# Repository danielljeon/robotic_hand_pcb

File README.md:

# robotic_hand_pcb

Robotic hand project for actuators/power electronics and sensors/instrumentation
university courses (PCB hardware).

STM32F446RE firmware
repo: [robotic_hand](https://github.com/danielljeon/robotic_hand).

- System architecture is explained in further detail in this software repo.

---

<details markdown="1">
  <summary>Table of Contents</summary>

<!-- TOC -->
* [robotic_hand_pcb](#robotic_hand_pcb)
  * [1 Overview](#1-overview)
  * [2 Board Specifications](#2-board-specifications)
    * [2.1 Connectors](#21-connectors)
      * [2.1.1 BAT+/VIN Terminals](#211-batvin-terminals)
    * [2.2 Switches & Jumpers](#22-switches--jumpers)
    * [2.3 Test Pads](#23-test-pads)
  * [3 Release Notes](#3-release-notes)
    * [3.1 v0.1.0](#31-v010)
    * [3.2 v0.2.0](#32-v020)
  * [4 Development Process](#4-development-process)
    * [4.1 Simulations: OrCAD X (PSpice)](#41-simulations-orcad-x-pspice)
    * [4.2 PCB Design: KiCad](#42-pcb-design-kicad)
    * [4.3 Firmware: CLion and STM32CubeMX](#43-firmware-clion-and-stm32cubemx)
    * [4.4. Version Control: GitHub](#44-version-control-github)
  * [5 Switching Buck Regulator](#5-switching-buck-regulator)
    * [5.1 Load Current Estimation](#51-load-current-estimation)
    * [5.2 Switching Frequency Selection](#52-switching-frequency-selection)
    * [5.3 Inductor Selection](#53-inductor-selection)
    * [5.4 Output Capacitor Selection](#54-output-capacitor-selection)
    * [5.5 Input Capacitor Selection](#55-input-capacitor-selection)
    * [5.6 PSpice Simulation](#56-pspice-simulation)
      * [5.6.1 Schematic](#561-schematic)
      * [5.6.2 Output](#562-output)
      * [5.6.3 Fast Fourier Transform (FFT)](#563-fast-fourier-transform-fft)
  * [💖 Sponsors](#-sponsors)
    * [PCBWay](#pcbway)
      * [Why PCBWay?](#why-pcbway)
<!-- TOC -->

</details>

---

This project is sponsored by **PCBWay**. You can learn more about their valuable
support here: [💖 Sponsors/PCBWay](#pcbway).

---

## 1 Overview

|                        Hand Assembly Back                         |                         Hand Assembly Front                         |
|:-----------------------------------------------------------------:|:-------------------------------------------------------------------:|
|  |  |

|                                 Top                                 |                                  Bottom                                   |
|:-------------------------------------------------------------------:|:-------------------------------------------------------------------------:|
|           |           |
|  |  |

- Pictures show v0.1.0 production run.

---

## 2 Board Specifications

### 2.1 Connectors

| Connector          |  Ref  | Description                                                                                                              |
|--------------------|:-----:|--------------------------------------------------------------------------------------------------------------------------|
| VL53L4CD Breakout  | (J)U6 | Breakout connector for TOF sensor                                                                                        |
| USB-C 5 V power    |  J1   | Power only USB-C, primary 5 V source                                                                                     |
| Tag-Connect TC2050 |  J2   | Programming/debug connector                                                                                              |
| BAT+/VIN           |  J3   | Pin 1: (GND) Ground, Pin 2: (BAT+) Power supply (> 5 V, <= 36 V), see [2.1.1 BAT+/VIN Terminals](#211-batvin-terminals). |
| 5V Breakout        |  J4   | 5 V analog input 7                                                                                                       |
| BOOT0 jumper       |  J5   | Open for run flash memory (pull-down on open)                                                                            |
| UART Breakout      |  J6   | General purpose UART breakout                                                                                            |
| WS2812B PWM LEDs   |  J7   | 5 V Addressable LED breakout                                                                                             |
| ADC 1              |  J8   | 5 V analog input 1                                                                                                       |
| ADC 2              |  J9   | 5 V analog input 2                                                                                                       |
| ADC 3              |  J10  | 5 V analog input 3                                                                                                       |
| ADC 4              |  J11  | 5 V analog input 4                                                                                                       |
| ADC 5              |  J12  | 5 V analog input 5                                                                                                       |
| ADC 6              |  J13  | 5 V analog input 6                                                                                                       |
| ADC 7              |  J14  | 5 V analog input 7                                                                                                       |
| Unipolar Motor 1   |  J15  | Robotic finger 1 motor                                                                                                   |
| Unipolar Motor 2   |  J16  | Robotic finger 2 motor                                                                                                   |
| Unipolar Motor 3   |  J17  | Robotic finger 3 motor                                                                                                   |
| Unipolar Motor 4   |  J18  | Robotic finger 4 motor                                                                                                   |
| Unipolar Motor 5   |  J19  | Robotic finger 5 motor                                                                                                   |

- All generic breakout connectors are standard 2.54 mm pitch Harwin connectors
  except for the BAT+/VIN connector.

#### 2.1.1 BAT+/VIN Terminals

The battery or supply terminals for the LMR51430 (5 V) buck regulator are custom
sizes designed for higher gauge wires.

The **recommended supply voltage is 12 V**, however the LMR51430 has a
theoretical range up to 36 volts.

- Hole: 1.5 mm diameter.
- Pad: 2.5 mm diameter.
- Pitch: 4 mm (center-to-center distance).

### 2.2 Switches & Jumpers

| Switch/Jumper         | Ref | Description                                           |
|-----------------------|:---:|-------------------------------------------------------|
| MCU NRESET switch     | SW1 | Generic 6 mm TH button, push to reset                 |
| VL53L4CD breakout INT | JP1 | Open = no breakout, closed = bridge breakout INT line |
| BNO085 clock select   | JP2 | Open = crystal, closed = external/internal            |

### 2.3 Test Pads

| Test Pad        | Ref | Description                                                       |
|-----------------|:---:|-------------------------------------------------------------------|
| LMR51430 enable | TP1 | Buck converter enable pin (tied to VIN Battery supply by default) |

---

## 3 Release Notes

### 3.1 v0.1.0

- Production oriented 4-layer board variant.
    - Designed for single production run given course project requirement.
- Order date: 2025/02/23.
- Order number: `W837000ASB9`.

### 3.2 v0.2.0

- Updated PCB for hand reworks on `v0.1.0` to get full ADS114S08 feature
  functionality.
    - Requires software changes for this functionality, thus semantic versioning
      minor value was moved to `2`.
    - Rework shown in picture below:

---

## 4 Development Process

### 4.1 Simulations: OrCAD X (PSpice)

[OrCAD X (PSpice)](https://www.cadence.com/en_US/home/tools/pcb-design-and-analysis/analog-mixed-signal-simulation/pspice.html)
by Cadence was used for circuit simulation and evaluation.

Since this project relies heavily on Texas Instruments (TI) components (ADC ICs,
Darlington transistor arrays, and buck regulators), PSpice was chosen for design
verification and virtual testing. TI provides official PSpice models, making
simulations more accurate and reliable.

Initially, [PSpice for TI](https://www.ti.com/tool/PSPICE-FOR-TI) (a free
version limited to TI parts) was used. Upgrading to OrCAD X enabled full
compatibility and broader simulation capabilities.

### 4.2 PCB Design: KiCad

[KiCad](https://www.kicad.org/) was chosen for PCB design due to its ease of use
as a free, open-source software. Additionally, prior experience and personal
preference played a key role in the decision.

### 4.3 Firmware: CLion and STM32CubeMX

[CLion](https://www.jetbrains.com/clion/)
and [STM32CubeMX](https://www.st.com/en/development-tools/stm32cubemx.html) from
STMicroelectronics were selected based on prior experience and personal
preference. STM32CubeMX is utilized for initial component selection, pin
configuration, and HAL software generation, while CLion is used for general C
firmware development. For more details,
see [robotic_hand](https://github.com/danielljeon/robotic_hand).

### 4.4. Version Control: GitHub

[GitHub](https://github.com/) was chosen for its efficiency in version control
and support for Actions automations. These automations facilitated testing,
validation, and various manufacturing-related processes for both hardware and
software development.

---

## 5 Switching Buck Regulator

The LMR51430 was chosen for its wide input voltage range of 4.5 V to 36 V, high
output current of 3 A and overall efficiency.

> Datasheet: Datasheet: LMR51430 SLUSEF4A – JUNE 2022 – REVISED NOVEMBER 2022.

> Big thanks, as always, to the amazing publicly available resources online 👑:
> 1. [Switching Regulator PCB Design - Phil's Lab #60](https://www.youtube.com/watch?v=AmfLhT5SntE)
> 2. [Switching Regulator Component Selection & Sizing - Phil's Lab #71](https://www.youtube.com/watch?v=FqT_Ofd54fo)

### 5.1 Load Current Estimation

The expected current load is as follows:

| Load              | Current | n |
|-------------------|---------|---|
| Motors + drivers  | 500 mA  | 5 |
| WS2812B LEDs      | 60 mA   | 1 |
| 3.3 V ICs via LDO | 100 mA  | 1 |

Approximate total current draw: 2660 mA = 2.66 A at 5 V.

In a real-world engineering scenario, current draw would be estimated using more
accurate models and measured across various revisions of development boards.
However, due to budget constraints and the need to support future higher-voltage
applications, a 3 A buck regulator was chosen, as it is a commonly available and
cost-effective option.

While this provides only an 11% safety margin, it was deemed acceptable for
early research and educational purposes. In the worst-case scenario, the board
can also be powered by an external 5 V power supply if needed.

### 5.2 Switching Frequency Selection

The LMR51430 is capable of 500 kHz and 1.1 MHz switching. The design opted for
the 500 kHz configuration for reduced switching noise and its application of
motor current driving. A lower switching frequency would theoretically reduce
switching losses and improve efficiency at high current draw.

### 5.3 Inductor Selection

The following calculations are based on the recommendations provided in the
LMR51430 datasheet.

The desired peak-to-peak ripple current is given by the following:

$$\Delta i_L = \frac{V_{OUT} \times \left( V_{IN \space MAX} - V_{OUT} \right)}{V_{IN \space MAX} \times L \times f_{SW}}$$

- $L$ = Inductance driving ripple.

The minimum inductor specification is given by:

$$L_{min} = \frac{V_{\text{IN MAX}} - V_{\text{OUT}}}{I_{\text{OUT}} \times K_{\text{IND}}} \times \frac{V_{\text{OUT}}}{V_{\text{IN MAX}} \times f_{\text{SW}}}$$
$$L_{min} = \frac{12 \space \text{V} - 5 \space \text{V}}{3 \space \text{A} \times 0.3} \times \frac{5 \space \text{V}}{12 \space \text{V} \times 500 \times 10^{3} \space \text{Hz}}$$
$$L_{min} = 6.84 \times 10^{-6} \space \text{H} = 6.84 \space \mathrm{\mu H}$$

- $K_{IND}$ = Coefficient representing the inductor ripple current as a fraction
  of the maximum output current, utilizing 0.3 for this project.
    - > A reasonable value of KIND must be 20% to 60% of maximum IOUT supported
      > by the converter.
      >
      > - Datasheet section: _9.2.2.4 Inductor Selection_.
- $f_{\text{SW}}$ = Switching frequency, 500 kHz chosen.
- $V_{\text{IN MAX}}$ = Input voltage, expected 12 V with ±1 V, 13 V.
- $V_{\text{OUT}}$ = Output voltage, 5 V.
- $I_{\text{OUT}}$ = Output current, approximately 3 A.

> During an instantaneous over-current operation event, the RMS and peak
> inductor current can be high. The inductor saturation current must be higher
> than peak current limit level.
>
> In general, choose lower inductance in switching power supplies because it
> usually corresponds to faster transient response, smaller DCR, and reduced
> size for more compact designs. Too low of an inductance can generate too large
> of an inductor current ripple such that over-current protection at the full
> load can be falsely triggered and generates more inductor core loss because
> the current ripple is larger. Larger inductor current ripple also implies
> larger output voltage ripple with the same output capacitors. With peak
> current mode control,ensure there is an adequate amount of inductor ripple
> current. A larger inductor ripple current improves the comparator
> signal-to-noise ratio.
>
> - Datasheet section: _9.2.2.4 Inductor Selection_.

The final minimum inductance value of 6.84 μH closely matches the example
application values provided for a 12V input and 5V output, which uses 6.8 μH.

### 5.4 Output Capacitor Selection

> Minimize the output capacitance to keep cost and size down. The output
> capacitor or capacitors, COUT, must be chosen with care because it directly
> affects the steady state output voltage ripple, loop stability, and output
> voltage overshoot and undershoot during load current transient. The output
> voltage ripple is essentially composed of two parts. One part is caused by the
> inductor ripple current flowing through the Equivalent Series Resistance (ESR)
> of the output capacitors ... The other part is caused by the inductor current
> ripple charging and discharging the output capacitors.
>
> - Datasheet section: _9.2.2.5 Output Capacitor Selection_.

Inductor current ripple flowing through the ESR is given by:

$$\Delta V_{\text{OUT ESR}} = \Delta i_L \times \text{ESR} = K_{\text{IND}} \times I_{\text{OUT}} \times \text{ESR}$$

Inductor current ripple charging and discharging the output capacitors is given
by:

$$\Delta V_{\text{OUT C}} = \frac{\Delta i_L}{8 \times f_{\text{SW}} \times C_{\text{OUT}}} = \frac{K_{\text{IND}} \times I_{\text{OUT}}}{8 \times f_{\text{SW}} \times C_{\text{OUT}}}$$

- $K_{\text{IND}}$ = target ripple ratio of the inductor
  current ($\Delta i L / I_{\text{OUT}}$).

The minimum output capacitance needed for a specified output voltage overshoot
and undershoot is given by:

$$C_{\text{OUT}} > \frac{1}{2} \times \frac{8 \times (I_{\text{OH}} - I_{\text{OL}})}{f_{\text{SW}} \times \Delta V_{\text{OUT SHOOT}}}$$

- $I_{\text{OL}}$ = low level output current during load transient.
- $I_{\text{OH}}$ = high level output current during load transient.
- $V_{\text{OUT SHOOT}}$ = target output voltage overshoot or undershoot.

For this project a target output ripple is arbitrarily set for 30 mV and the
ripple ratio of inductor current is set to 0.3.

- $\Delta V_{\text{OUT ESR}} = \Delta V_{\text{OUT C}} = 30 mV$
- $K_{\text{IND}} = 0.3$

This yields ESR < 75 mΩ and output capacitance > 14 μF.

### 5.5 Input Capacitor Selection

> The LMR51430 device requires a high frequency input decoupling capacitor or
> capacitor. The typical recommended value for the high frequency decoupling
> capacitor is 4.7 μF or higher. TI recommends a high-quality ceramic type X5R
> or X7R with a sufficient voltage rating. The voltage rating must be greater
> than the maximum input voltage. To compensate the derating of ceramic
> capacitors, TI recommends a voltage rating of twice the maximum input voltage.
>
> - Datasheet section: _9.2.2.5 Output Capacitor Selection_.

### 5.6 PSpice Simulation

Due to the limited availability of publicly accessible PSpice models, the
LMR51420 model was used instead. Based on datasheet specifications, the 2A
variant of the LMR514x0 series appears largely similar, with the primary
difference being the requirement for a 10 μH inductor.

#### 5.6.1 Schematic

To simulate sudden current loads, a 3.3 Ω load (drawing 1.5 A at 5 V) is added
and set to switch at 4.2 ms. The switch has a transition time of 15 μs.

#### 5.6.2 Output

#### 5.6.3 Fast Fourier Transform (FFT)

For this simulation run, the fundamental frequency was found to be 492.400 kHz
with a resultant amplitude of 1.1316. Due to the short simulation duration, the
time required to ramp up to the final voltage, and the handling of sudden loads,
it is hypothesized that the FFT results deviate slightly from the expected 500
kHz.

---

## 💖 Sponsors

### PCBWay

This project is sponsored by [**PCBWay**](https://www.pcbway.com), whose PCB
manufacturing services are essential in producing high-quality prototypes for
its development. Their support ensures reliable boards that meet the project's
demands.

#### Why PCBWay?

PCBWay stands out for their exceptional services and commitment to the
community:

- **PCB Manufacturing**: High-quality fabrication with options for multilayer,
  rigid-flex, and advanced designs.
- **PCB Assembly**: Comprehensive solutions, including soldering, component
  sourcing, and assembly.
- **CNC Machining & 3D Printing**: Additional prototyping options to support
  complete product development.
- **Fast Turnaround**: Reliable and quick production times to keep projects on
  schedule.
- **Support for Open Source & Education**: PCBWay actively sponsors projects and
  provides educational resources like tutorials, videos, and documentation,
  empowering developers and hobbyists.
    - This commitment to education and open-source advocacy was a key factor in
      choosing them as a partner 🙂.

Their dedication to professional-grade services and fostering innovation makes
PCBWay an invaluable partner in bringing this project to life.

Learn more here: [Why PCBWay?](https://www.pcbway.com/why.html)

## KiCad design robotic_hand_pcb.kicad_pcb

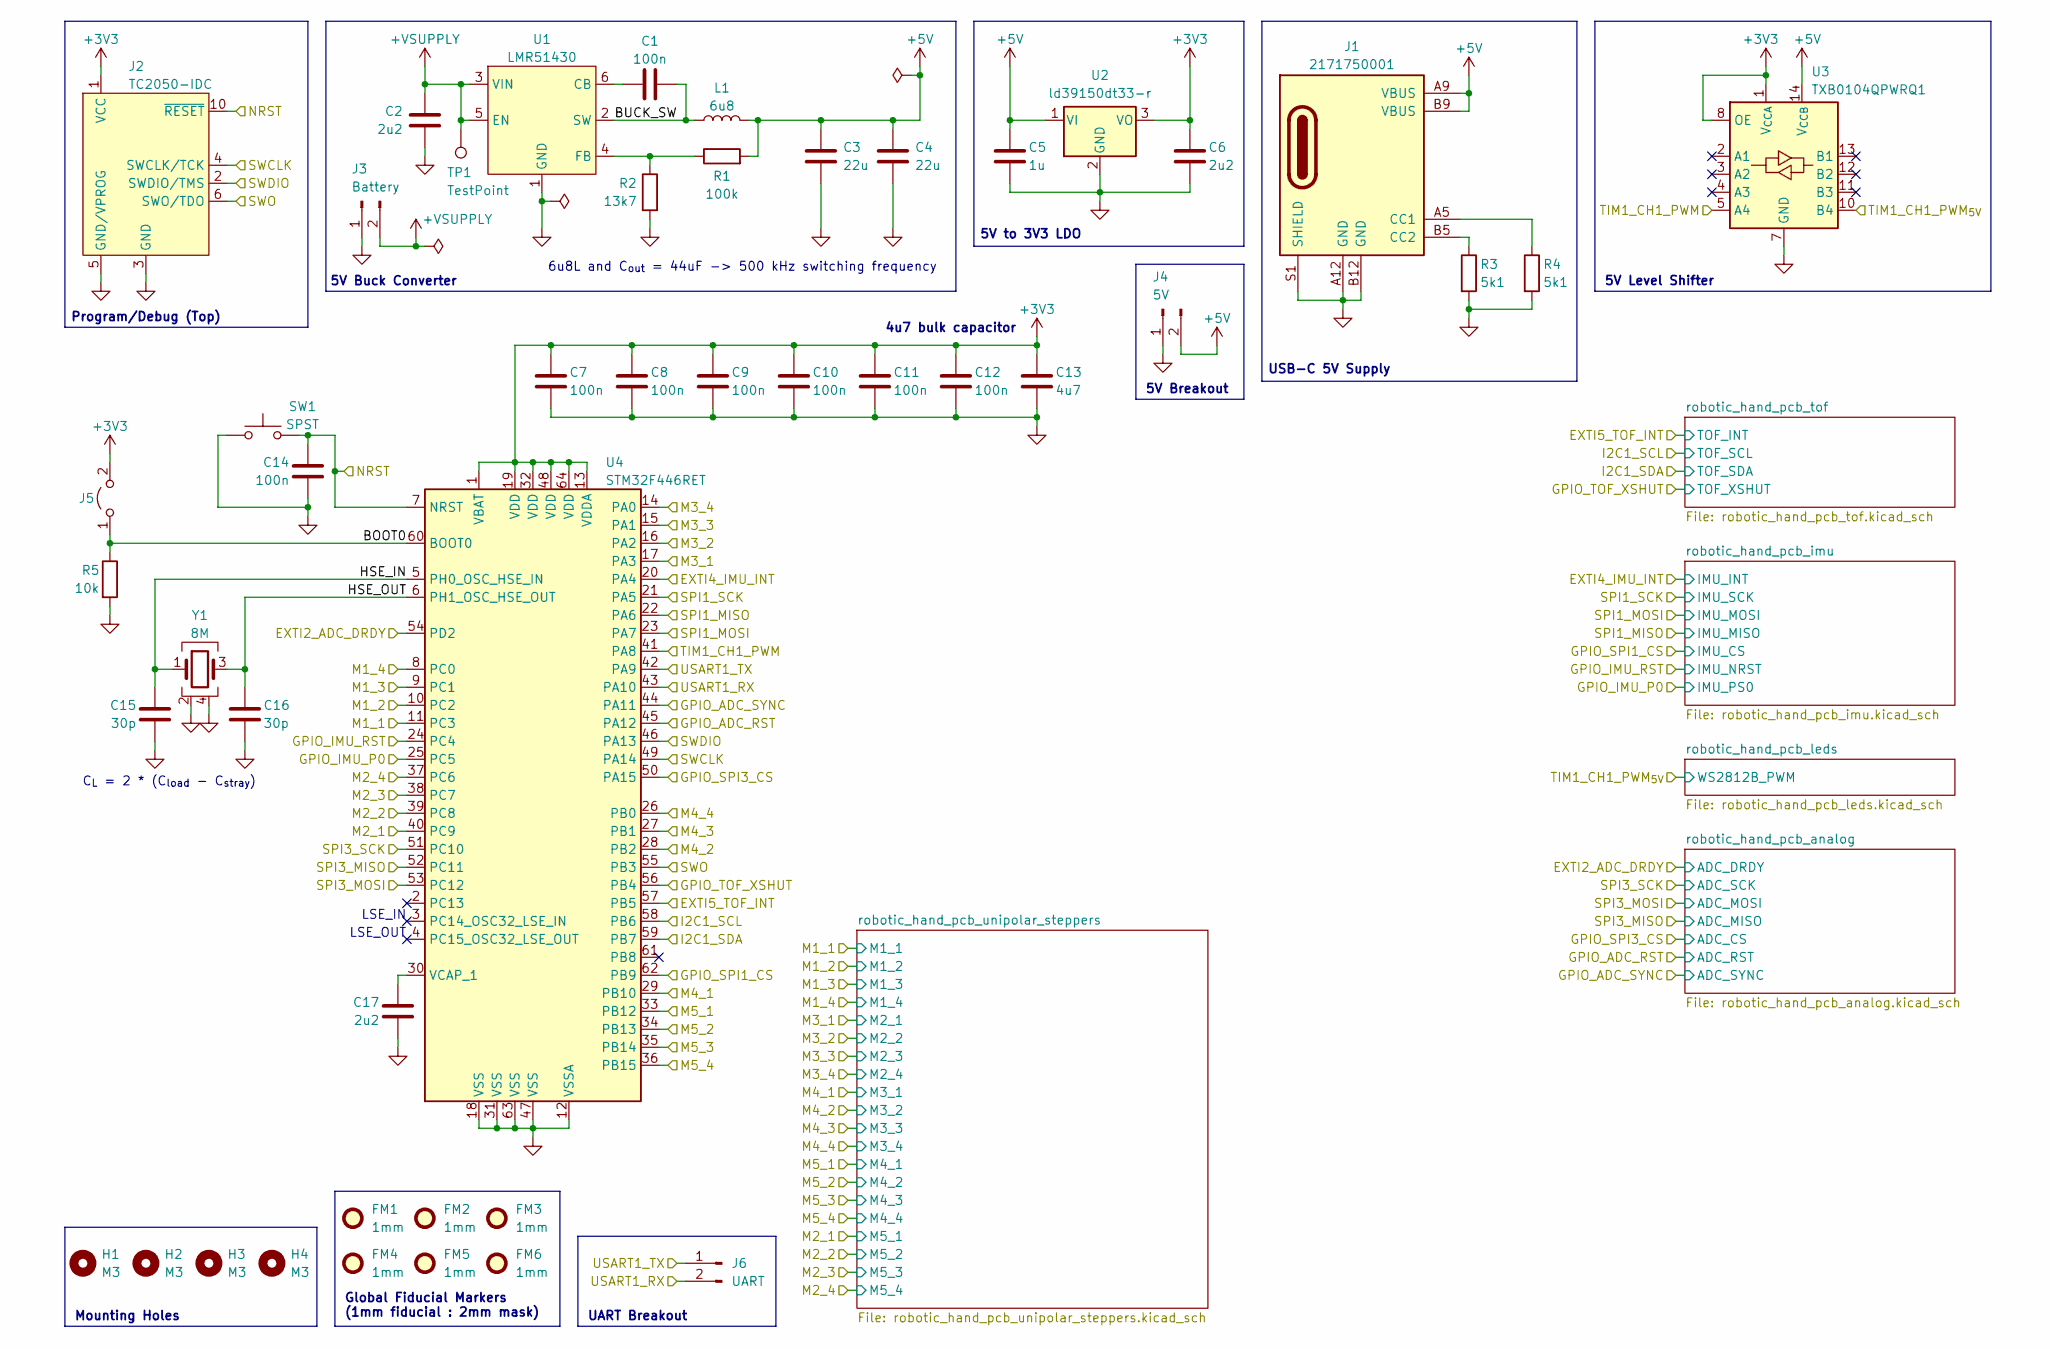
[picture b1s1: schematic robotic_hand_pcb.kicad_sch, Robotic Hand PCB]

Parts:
C1: 100n; C_0805_2012Metric
C2: 2u2; C_0805_2012Metric
C3, C4: 22u; C_1210_3225Metric
C5: 1u; C_0603_1608Metric
C6, C17: 2u2; C_0603_1608Metric
C7, C8, C9, C10, C11, C12, C14: 100n; C_0603_1608Metric
C13: 4u7; C_0603_1608Metric
C15, C16: 30p; C_0402_1005Metric
FM1, FM2, FM3, FM4, FM5, FM6: 1mm; Fiducial_1mm_Mask2mm
H1, H2, H3, H4: M3; MountingHole_3.2mm_M3
J1: 2171750001; molex_2171750001_usb_c_6p; Manufacturer Part Number 2171750001
J2: TC2050-IDC; tag_connect_tc2050-idc; Manufacturer Part Number TC2050-IDC
J3: Battery; battery
J4: 5V; PinHeader_1x02_P2.54mm_Vertical
J5: harwin_2p_2-54_jumper_open; Manufacturer Part Number M20-9990246
J6: UART; PinHeader_1x02_P2.54mm_Vertical
L1: 6u8; vishay_ihlp-2525cz
R1: 100k; R_0603_1608Metric
R2: 13k7; R_0603_1608Metric
R3, R4: 5k1; R_0603_1608Metric
R5: 10k; R_0603_1608Metric
SW1: SPST; SW_PUSH_6mm
TP1: TestPoint; TestPoint_Pad_D2.5mm
U1: LMR51430; lmr51430; Manufacturer Part Number LMR51430
U2: ld39150dt33-r; to-252-2_dpak-2-leg; Manufacturer Part Number LD39150DT33-R
U3: TXB0104QPWRQ1; txb0104qpwrq1; Manufacturer Part Number TXB0104QPWRQ1
U4: STM32F446RET; LQFP-64_10x10mm_P0.5mm; Manufacturer Part Number STM32F446RE
Y1: 8M; ecs_ecx-64; Manufacturer Part Number ECS-80-18-23B-JTN-TR

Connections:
+3V3: C6.1, C7.1, C8.1, C9.1, C10.1, C11.1, C12.1, C13.1, J2.1 (VCC), J5.2, U2.3 (VO), U3.1 (V_{CCA}), U3.8 (OE), U4.1 (VBAT), U4.13 (VDDA), U4.19 (VDD), U4.32 (VDD), U4.48 (VDD), U4.64 (VDD); also elsewhere on the board
+5V: C3.2, C4.2, C5.1, J1.A9 (VBUS), J1.B9 (VBUS), J4.2, L1.2, R1.2, U2.1 (VI), U3.14 (V_{CCB}); also elsewhere on the board
+VSUPPLY: C2.1, J3.2, TP1.1, U1.3 (VIN), U1.5 (EN)
/BOOT0: J5.1, R5.1, U4.60 (BOOT0)
/BUCK_SW: C1.2, L1.1, U1.2 (SW)
/EXTI2_ADC_DRDY: U4.54 (PD2); also elsewhere on the board
/EXTI4_IMU_INT: U4.20 (PA4); also elsewhere on the board
/EXTI5_TOF_INT: U4.57 (PB5); also elsewhere on the board
/GPIO_ADC_RST: U4.45 (PA12); also elsewhere on the board
/GPIO_ADC_SYNC: U4.44 (PA11); also elsewhere on the board
/GPIO_IMU_P0: U4.25 (PC5); also elsewhere on the board
/GPIO_IMU_RST: U4.24 (PC4); also elsewhere on the board
/GPIO_SPI1_CS: U4.62 (PB9); also elsewhere on the board
/GPIO_SPI3_CS: U4.50 (PA15); also elsewhere on the board
/GPIO_TOF_XSHUT: U4.56 (PB4); also elsewhere on the board
/HSE_IN: C15.1, U4.5 (PH0_OSC_HSE_IN), Y1.1
/HSE_OUT: C16.1, U4.6 (PH1_OSC_HSE_OUT), Y1.3
/I2C1_SCL: U4.58 (PB6); also elsewhere on the board
/I2C1_SDA: U4.59 (PB7); also elsewhere on the board
/M1_1: U4.11 (PC3); also elsewhere on the board
/M1_2: U4.10 (PC2); also elsewhere on the board
/M1_3: U4.9 (PC1); also elsewhere on the board
/M1_4: U4.8 (PC0); also elsewhere on the board
/M2_1: U4.40 (PC9); also elsewhere on the board
/M2_2: U4.39 (PC8); also elsewhere on the board
/M2_3: U4.38 (PC7); also elsewhere on the board
/M2_4: U4.37 (PC6); also elsewhere on the board
/M3_1: U4.17 (PA3); also elsewhere on the board
/M3_2: U4.16 (PA2); also elsewhere on the board
/M3_3: U4.15 (PA1); also elsewhere on the board
/M3_4: U4.14 (PA0); also elsewhere on the board
/M4_1: U4.29 (PB10); also elsewhere on the board
/M4_2: U4.28 (PB2); also elsewhere on the board
/M4_3: U4.27 (PB1); also elsewhere on the board
/M4_4: U4.26 (PB0); also elsewhere on the board
/M5_1: U4.33 (PB12); also elsewhere on the board
/M5_2: U4.34 (PB13); also elsewhere on the board
/M5_3: U4.35 (PB14); also elsewhere on the board
/M5_4: U4.36 (PB15); also elsewhere on the board
/NRST: C14.2, J2.10 (~RESET), SW1.2, U4.7 (NRST)
/SPI1_MISO: U4.22 (PA6); also elsewhere on the board
/SPI1_MOSI: U4.23 (PA7); also elsewhere on the board
/SPI1_SCK: U4.21 (PA5); also elsewhere on the board
/SPI3_MISO: U4.52 (PC11); also elsewhere on the board
/SPI3_MOSI: U4.53 (PC12); also elsewhere on the board
/SPI3_SCK: U4.51 (PC10); also elsewhere on the board
/SWCLK: J2.4 (SWCLK/TCK), U4.49 (PA14)
/SWDIO: J2.2 (SWDIO/TMS), U4.46 (PA13)
/SWO: J2.6 (SWO/TDO), U4.55 (PB3)
/TIM1_CH1_PWM: U3.5 (A4), U4.41 (PA8)
/TIM1_CH1_PWM_{5V}: U3.10 (B4); also elsewhere on the board
/USART1_RX: J6.2, U4.43 (PA10)
/USART1_TX: J6.1, U4.42 (PA9)
GND: C2.2, C3.1, C4.1, C5.2, C6.2, C7.2, C8.2, C9.2, C10.2, C11.2, C12.2, C13.2, C14.1, C15.2, C16.2, C17.2, J1.A12 (GND), J1.B12 (GND), J1.S1 (SHIELD), J2.3 (GND), J2.5 (GND/VPROG), J3.1, J4.1, R2.2, R3.2, R4.2, R5.2, SW1.1, U1.1 (GND), U2.2 (GND), U3.7 (GND), U4.12 (VSSA), U4.18 (VSS), U4.31 (VSS), U4.47 (VSS), U4.63 (VSS), Y1.2, Y1.4; also elsewhere on the board
unnamed: J1.A5 (CC1), R4.1
unnamed: J1.B5 (CC2), R3.1
unnamed: C1.1, U1.6 (CB)
unnamed: R1.1, R2.1, U1.4 (FB)
unnamed: C17.1, U4.30 (VCAP_1)

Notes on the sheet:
LSE_OUT
5V Buck Converter
5V Breakout
4u7 bulk capacitor
Program/Debug (Top)
UART Breakout
Global Fiducial Markers (1mm fiducial : 2mm mask)
C_{L} = 2 * (C_{load} - C_{stray})
USB-C 5V Supply
LSE_IN
Mounting Holes
5V Level Shifter
6u8L and C_{out} = 44uF -> 500 kHz switching frequency
5V to 3V3 LDO

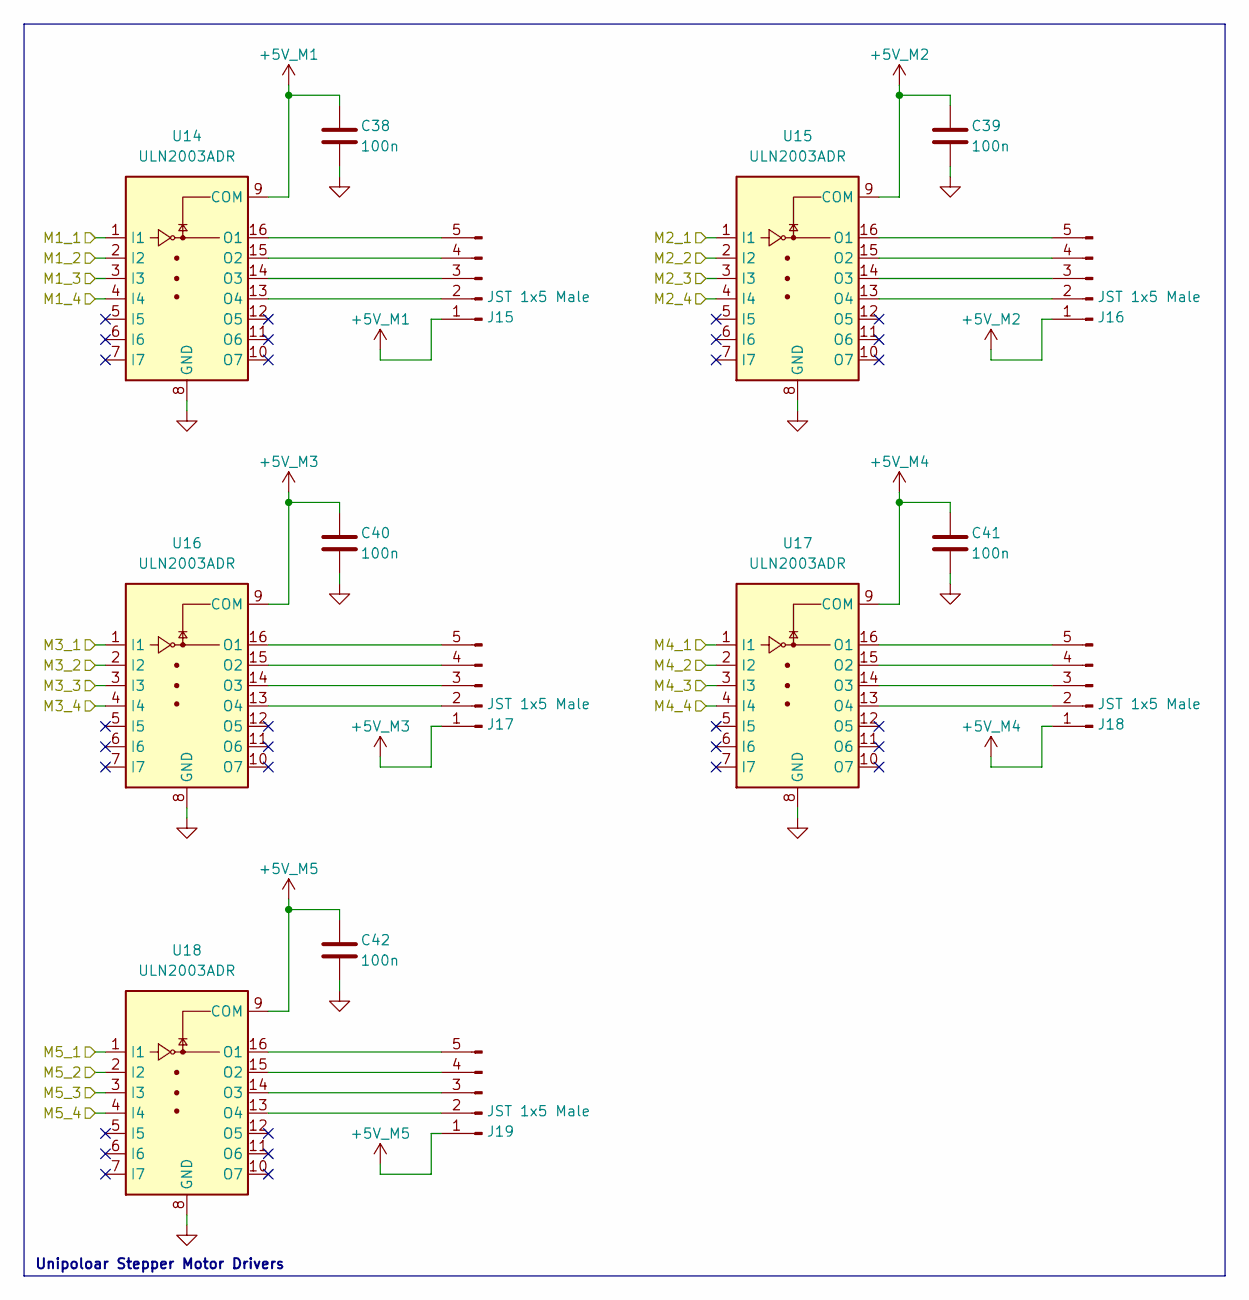
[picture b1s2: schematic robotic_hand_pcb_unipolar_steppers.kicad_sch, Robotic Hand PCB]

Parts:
C38, C39, C40, C41, C42: 100n; C_0603_1608Metric
J15, J16, J17, J18, J19: JST 1x5 Male; PinHeader_1x05_P2.54mm_Vertical
U14, U15, U16, U17, U18: ULN2003ADR; SOIC-16_3.9x9.9mm_P1.27mm

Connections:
+5V_M1: C38.1, J15.1, U14.9 (COM); also elsewhere on the board
+5V_M2: C39.1, J16.1, U15.9 (COM); also elsewhere on the board
+5V_M3: C40.1, J17.1, U16.9 (COM); also elsewhere on the board
+5V_M4: C41.1, J18.1, U17.9 (COM); also elsewhere on the board
+5V_M5: C42.1, J19.1, U18.9 (COM); also elsewhere on the board
/M1_1: U14.1 (I1); also elsewhere on the board
/M1_2: U14.2 (I2); also elsewhere on the board
/M1_3: U14.3 (I3); also elsewhere on the board
/M1_4: U14.4 (I4); also elsewhere on the board
/M2_1: U18.1 (I1); also elsewhere on the board
/M2_2: U18.2 (I2); also elsewhere on the board
/M2_3: U18.3 (I3); also elsewhere on the board
/M2_4: U18.4 (I4); also elsewhere on the board
/M3_1: U15.1 (I1); also elsewhere on the board
/M3_2: U15.2 (I2); also elsewhere on the board
/M3_3: U15.3 (I3); also elsewhere on the board
/M3_4: U15.4 (I4); also elsewhere on the board
/M4_1: U16.1 (I1); also elsewhere on the board
/M4_2: U16.2 (I2); also elsewhere on the board
/M4_3: U16.3 (I3); also elsewhere on the board
/M4_4: U16.4 (I4); also elsewhere on the board
/M5_1: U17.1 (I1); also elsewhere on the board
/M5_2: U17.2 (I2); also elsewhere on the board
/M5_3: U17.3 (I3); also elsewhere on the board
/M5_4: U17.4 (I4); also elsewhere on the board
GND: C38.2, C39.2, C40.2, C41.2, C42.2, U14.8 (GND), U15.8 (GND), U16.8 (GND), U17.8 (GND), U18.8 (GND); also elsewhere on the board
unnamed: J15.2, U14.13 (O4)
unnamed: J15.3, U14.14 (O3)
unnamed: J15.4, U14.15 (O2)
unnamed: J15.5, U14.16 (O1)
unnamed: J16.2, U15.13 (O4)
unnamed: J16.3, U15.14 (O3)
unnamed: J16.4, U15.15 (O2)
unnamed: J16.5, U15.16 (O1)
unnamed: J17.2, U16.13 (O4)
unnamed: J17.3, U16.14 (O3)
unnamed: J17.4, U16.15 (O2)
unnamed: J17.5, U16.16 (O1)
unnamed: J18.2, U17.13 (O4)
unnamed: J18.3, U17.14 (O3)
unnamed: J18.4, U17.15 (O2)
unnamed: J18.5, U17.16 (O1)
unnamed: J19.2, U18.13 (O4)
unnamed: J19.3, U18.14 (O3)
unnamed: J19.4, U18.15 (O2)
unnamed: J19.5, U18.16 (O1)

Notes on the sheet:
Unipoloar Stepper Motor Drivers

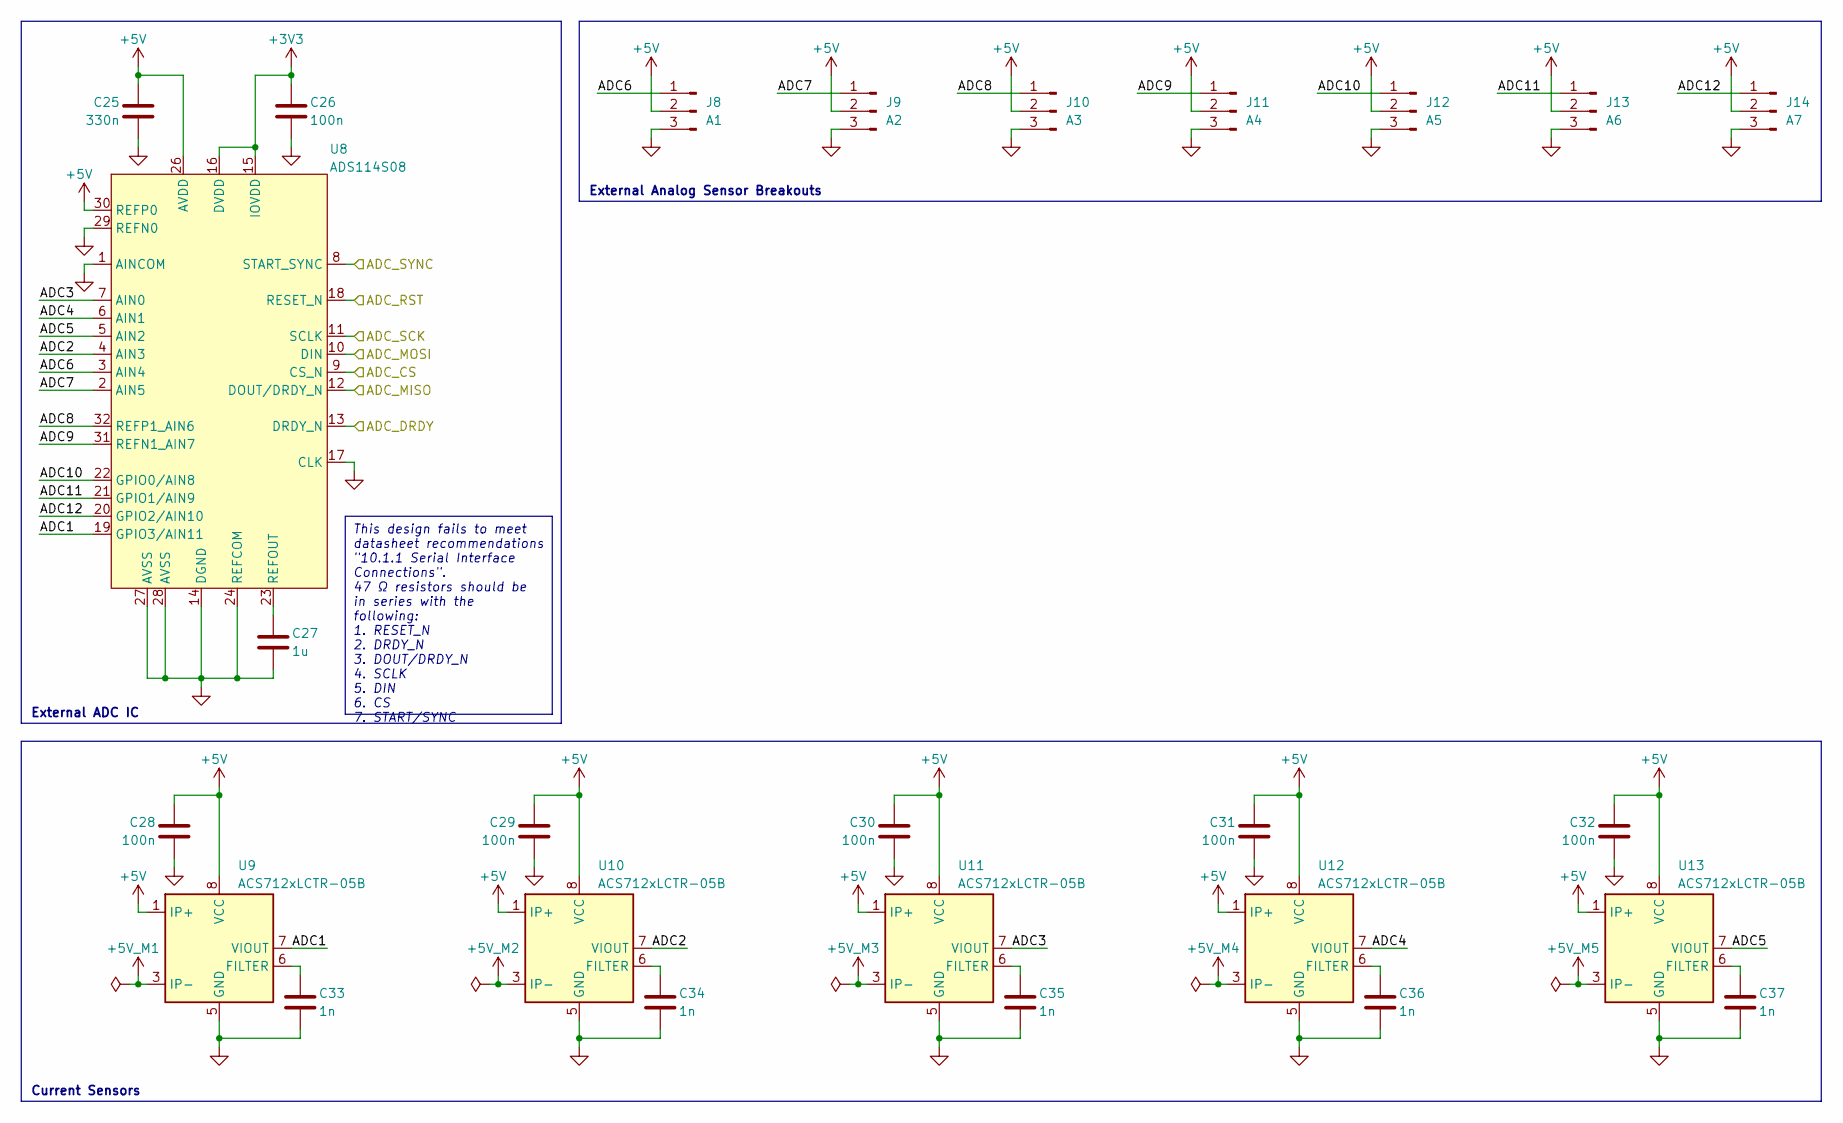
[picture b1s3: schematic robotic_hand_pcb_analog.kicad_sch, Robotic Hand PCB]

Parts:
C25: 330n; C_0603_1608Metric
C26, C28, C29, C30, C31, C32: 100n; C_0603_1608Metric
C27: 1u; C_0603_1608Metric
C33, C34, C35, C36, C37: 1n; C_0603_1608Metric
J8: A1; PinHeader_1x03_P2.54mm_Vertical
J9: A2; PinHeader_1x03_P2.54mm_Vertical
J10: A3; PinHeader_1x03_P2.54mm_Vertical
J11: A4; PinHeader_1x03_P2.54mm_Vertical
J12: A5; PinHeader_1x03_P2.54mm_Vertical
J13: A6; PinHeader_1x03_P2.54mm_Vertical
J14: A7; PinHeader_1x03_P2.54mm_Vertical
U8: ADS114S08; ads114s08_tqfp-32; Manufacturer Part Number ADS114S08
U9, U10, U11, U12, U13: ACS712xLCTR-05B; SOIC-8_3.9x4.9mm_P1.27mm

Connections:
+3V3: C26.2, U8.15 (IOVDD), U8.16 (DVDD); also elsewhere on the board
+5V: C25.2, C28.2, C29.2, C30.2, C31.2, C32.2, J8.2, J9.2, J10.2, J11.2, J12.2, J13.2, J14.2, U8.26 (AVDD), U8.30 (REFP0), U9.1 (IP+), U9.2 (IP+), U9.8 (VCC), U10.1 (IP+), U10.2 (IP+), U10.8 (VCC), U11.1 (IP+), U11.2 (IP+), U11.8 (VCC), U12.1 (IP+), U12.2 (IP+), U12.8 (VCC), U13.1 (IP+), U13.2 (IP+), U13.8 (VCC); also elsewhere on the board
+5V_M1: U9.3 (IP-), U9.4 (IP-); also elsewhere on the board
+5V_M2: U10.3 (IP-), U10.4 (IP-); also elsewhere on the board
+5V_M3: U11.3 (IP-), U11.4 (IP-); also elsewhere on the board
+5V_M4: U12.3 (IP-), U12.4 (IP-); also elsewhere on the board
+5V_M5: U13.3 (IP-), U13.4 (IP-); also elsewhere on the board
/EXTI2_ADC_DRDY: U8.13 (DRDY_N); also elsewhere on the board
/GPIO_ADC_RST: U8.18 (RESET_N); also elsewhere on the board
/GPIO_ADC_SYNC: U8.8 (START_SYNC); also elsewhere on the board
/GPIO_SPI3_CS: U8.9 (CS_N); also elsewhere on the board
/SPI3_MISO: U8.12 (DOUT/DRDY_N); also elsewhere on the board
/SPI3_MOSI: U8.10 (DIN); also elsewhere on the board
/SPI3_SCK: U8.11 (SCLK); also elsewhere on the board
/robotic_hand_pcb_analog/ADC1: U8.19 (GPIO3/AIN11), U9.7 (VIOUT)
/robotic_hand_pcb_analog/ADC2: U8.4 (AIN3), U10.7 (VIOUT)
/robotic_hand_pcb_analog/ADC3: U8.7 (AIN0), U11.7 (VIOUT)
/robotic_hand_pcb_analog/ADC4: U8.6 (AIN1), U12.7 (VIOUT)
/robotic_hand_pcb_analog/ADC5: U8.5 (AIN2), U13.7 (VIOUT)
/robotic_hand_pcb_analog/ADC6: J8.1, U8.3 (AIN4)
/robotic_hand_pcb_analog/ADC7: J9.1, U8.2 (AIN5)
/robotic_hand_pcb_analog/ADC8: J10.1, U8.32 (REFP1_AIN6)
/robotic_hand_pcb_analog/ADC9: J11.1, U8.31 (REFN1_AIN7)
/robotic_hand_pcb_analog/ADC10: J12.1, U8.22 (GPIO0/AIN8)
/robotic_hand_pcb_analog/ADC11: J13.1, U8.21 (GPIO1/AIN9)
/robotic_hand_pcb_analog/ADC12: J14.1, U8.20 (GPIO2/AIN10)
GND: C25.1, C26.1, C27.2, C28.1, C29.1, C30.1, C31.1, C32.1, C33.2, C34.2, C35.2, C36.2, C37.2, J8.3, J9.3, J10.3, J11.3, J12.3, J13.3, J14.3, U8.1 (AINCOM), U8.14 (DGND), U8.17 (CLK), U8.24 (REFCOM), U8.27 (AVSS), U8.28 (AVSS), U8.29 (REFN0), U9.5 (GND), U10.5 (GND), U11.5 (GND), U12.5 (GND), U13.5 (GND); also elsewhere on the board
unnamed: C27.1, U8.23 (REFOUT)
unnamed: C33.1, U9.6 (FILTER)
unnamed: C34.1, U10.6 (FILTER)
unnamed: C35.1, U11.6 (FILTER)
unnamed: C36.1, U12.6 (FILTER)
unnamed: C37.1, U13.6 (FILTER)

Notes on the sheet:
This design fails to meet datasheet recommendations "10.1.1 Serial Interface Connections". 47 Ω resistors should be in series with the following: 1. RESET_N 2. DRDY_N 3. DOUT/DRDY_N 4. SCLK 5. DIN 6. CS 7. START/SYNC
External Analog Sensor Breakouts
Current Sensors
External ADC IC

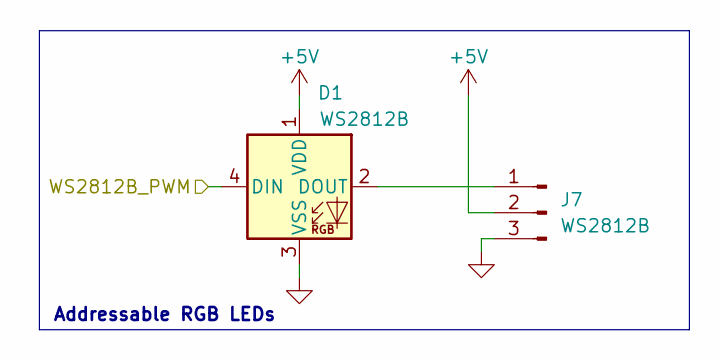
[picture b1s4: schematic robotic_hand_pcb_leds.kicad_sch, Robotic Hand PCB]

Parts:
D1: WS2812B; LED_WS2812B_PLCC4_5.0x5.0mm_P3.2mm
J7: WS2812B; PinHeader_1x03_P2.54mm_Vertical

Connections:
+5V: D1.1 (VDD), J7.2; also elsewhere on the board
/TIM1_CH1_PWM_{5V}: D1.4 (DIN); also elsewhere on the board
GND: D1.3 (VSS), J7.3; also elsewhere on the board
unnamed: D1.2 (DOUT), J7.1

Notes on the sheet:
Addressable RGB LEDs

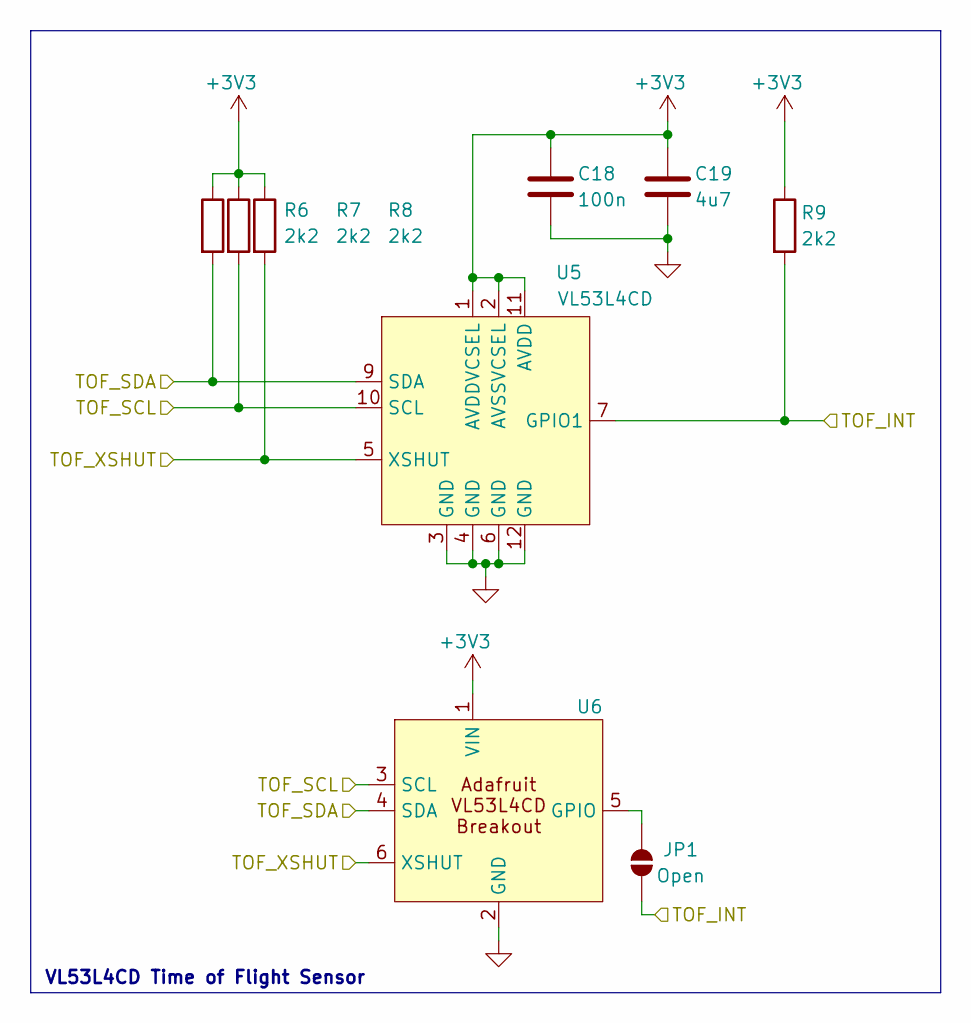
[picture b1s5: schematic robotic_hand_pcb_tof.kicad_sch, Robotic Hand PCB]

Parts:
C18: 100n; C_0603_1608Metric
C19: 4u7; C_0603_1608Metric
JP1: Open; SolderJumper-2_P1.3mm_Open_TrianglePad1.0x1.5mm
R6, R7, R8, R9: 2k2; R_0603_1608Metric
U5: VL53L4CD; vl53l4cd_lga12; Manufacturer Part Number VL53L4CDV0DH/1
U6: PinHeader_1x06_P2.54mm_Vertical; Manufacturer Part Number 5396

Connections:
+3V3: C18.1, C19.1, R6.1, R7.1, R8.1, R9.1, U5.1 (AVDDVCSEL), U5.2 (AVSSVCSEL), U5.11 (AVDD), U6.1 (VIN); also elsewhere on the board
/EXTI5_TOF_INT: JP1.1 (A), R9.2, U5.7 (GPIO1); also elsewhere on the board
/GPIO_TOF_XSHUT: R8.2, U5.5 (XSHUT), U6.6 (XSHUT); also elsewhere on the board
/I2C1_SCL: R7.2, U5.10 (SCL), U6.3 (SCL); also elsewhere on the board
/I2C1_SDA: R6.2, U5.9 (SDA), U6.4 (SDA); also elsewhere on the board
GND: C18.2, C19.2, U5.3 (GND), U5.4 (GND), U5.6 (GND), U5.12 (GND), U6.2 (GND); also elsewhere on the board
unnamed: JP1.2 (B), U6.5 (GPIO)

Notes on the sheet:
VL53L4CD Time of Flight Sensor

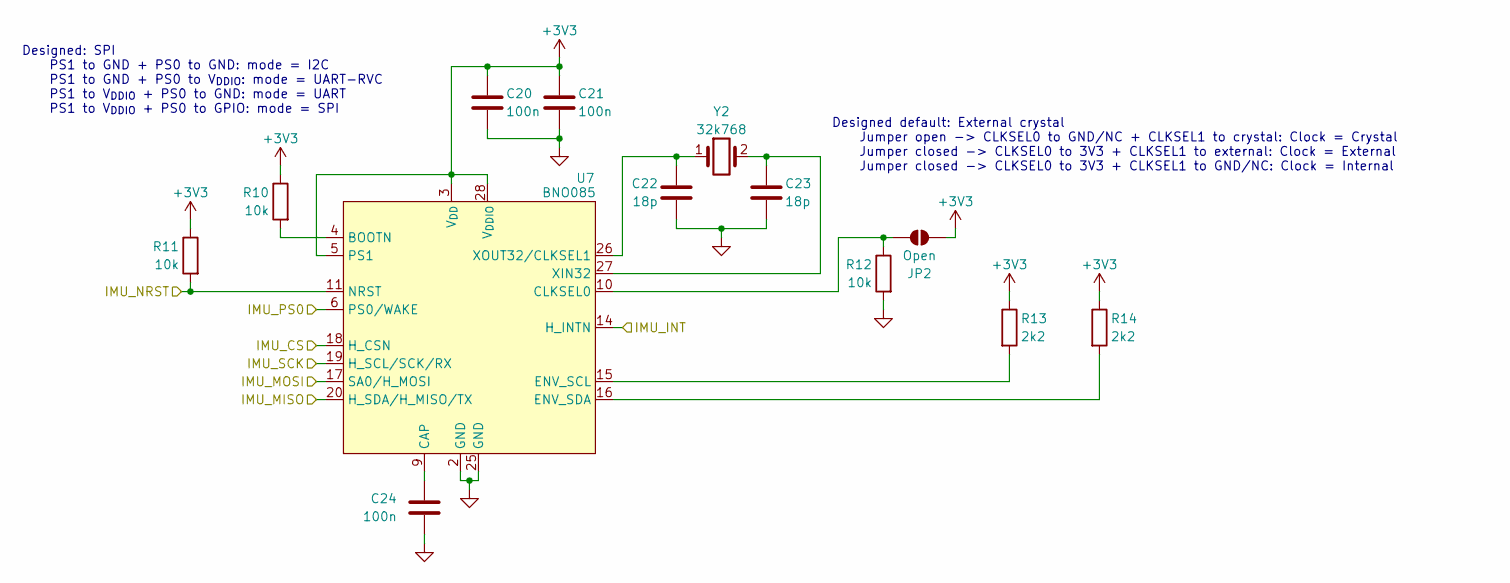
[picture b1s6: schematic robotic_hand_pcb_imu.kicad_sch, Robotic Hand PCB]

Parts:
C20, C21, C24: 100n; C_0603_1608Metric
C22, C23: 18p; C_0402_1005Metric
JP2: Open; SolderJumper-2_P1.3mm_Open_TrianglePad1.0x1.5mm
R10, R11, R12: 10k; R_0603_1608Metric
R13, R14: 2k2; R_0603_1608Metric
U7: BNO085; bno085; Manufacturer Part Number BNO085
Y2: 32k768; ecs_ecx-34r; Manufacturer Part Number ECS-.327-12.5-34R-C-TR

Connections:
+3V3: C20.1, C21.1, JP2.2 (B), R10.1, R11.1, R13.1, R14.1, U7.3 (V_{DD}), U7.5 (PS1), U7.28 (V_{DDIO}); also elsewhere on the board
/EXTI4_IMU_INT: U7.14 (H_INTN); also elsewhere on the board
/GPIO_IMU_P0: U7.6 (PS0/WAKE); also elsewhere on the board
/GPIO_IMU_RST: R11.2, U7.11 (NRST); also elsewhere on the board
/GPIO_SPI1_CS: U7.18 (H_CSN); also elsewhere on the board
/SPI1_MISO: U7.20 (H_SDA/H_MISO/TX); also elsewhere on the board
/SPI1_MOSI: U7.17 (SA0/H_MOSI); also elsewhere on the board
/SPI1_SCK: U7.19 (H_SCL/SCK/RX); also elsewhere on the board
GND: C20.2, C21.2, C22.2, C23.2, C24.2, R12.2, U7.2 (GND), U7.25 (GND); also elsewhere on the board
unnamed: JP2.1 (A), R12.1, U7.10 (CLKSEL0)
unnamed: R10.2, U7.4 (BOOTN)
unnamed: C24.1, U7.9 (CAP)
unnamed: R13.2, U7.15 (ENV_SCL)
unnamed: R14.2, U7.16 (ENV_SDA)
unnamed: C23.1, U7.27 (XIN32), Y2.2
unnamed: C22.1, U7.26 (XOUT32/CLKSEL1), Y2.1

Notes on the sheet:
Designed: SPI PS1 to GND + PS0 to GND: mode = I2C PS1 to GND + PS0 to V_{DDIO}: mode = UART-RVC PS1 to V_{DDIO} + PS0 to GND: mode = UART PS1 to V_{DDIO} + PS0 to GPIO: mode = SPI
Designed default: External crystal Jumper open -> CLKSEL0 to GND/NC + CLKSEL1 to crystal: Clock = Crystal Jumper closed -> CLKSEL0 to 3V3 + CLKSEL1 to external: Clock = External Jumper closed -> CLKSEL0 to 3V3 + CLKSEL1 to GND/NC: Clock = Internal
